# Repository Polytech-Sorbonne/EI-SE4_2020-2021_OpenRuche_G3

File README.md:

# Projet Open Ruche 2020-2021

Ce projet avait pour but de concevoir une ruche connectée afin de vérifier la production de miel des abeilles ainsi que leur bonne santé. Il a été conduit de     
septembre 2020 jusque janvier 2021 par quatre élèves de Polytech Sorbonne EISE4 : Clément Leboulenger, Edouard Matheu, Julie Rago et Clément Roger.

Notre ruche connectée comportait un PCB utilisant un microcontrôleur L432KC et implémentait différents capteurs et fonctionnalités:

  - Un capteur mesurant la température et l'humidité extérieures (le DHT22)
  - Un capteur mesurant la température intérieure (le DS18B20)
  - Une station météo mesurant la vitesse du vent (la LEXCA007)
  - Un capteur de poids (le HX711)
  - Un boitier étanche et facile d'utilisation comportant un bouton ON / OFF et une LED
  - Une mesure du pourcentage de la batterie
  - Une transmission des données sur une plateforme de visualisation des données (Ubidots)
  - Une application d'alertes envoyant des mails au client en cas de problème
 
Tous les codes sources ont été écrits sur mbed et sont disponibles dans le dossier [src](src) 

## Etape 1 : Prototype sur LABDEC

Afin de reproduire le prototype sur labdec il suffit de reproduire le branchement suivant puis de charger le code sur le microcontrôleur avec MBED.

## Etape 2 : Visualisation des données

Afin de vérifier le bon fonctionnement du prototype il faut pouvoir visualiser les données reçues. Une première solution est d'afficher ces dernières en série sur le terminal, néanmoins ceci n'est pas viable à long terme.

Nous avons utilisé la plateforme Ubidots qui permet une grande diversité de widgets. Pour cela il faut d'abord programmer le callback. Pour cela, nous vous invitons à suivre ce [tutoriel](https://www.google.com/url?sa=t&rct=j&q=&esrc=s&source=web&cd=&cad=rja&uact=8&ved=2ahUKEwjIvd3LoabuAhWS3eAKHfLjBFkQFjAAegQIAxAC&url=http%3A%2F%2Fhelp.ubidots.com%2Fen%2Farticles%2F924209-setup-your-sigfox-callback-to-talk-with-ubidots-cloud&usg=AOvVaw0ofYeG-8WFQl4HqIhr2u7Q).

Ensuite il suffira de programmer le callback comme suivant :

## Etape 3 : Création du PCB

Afin d'obtenir un produit final robuste et résistant il convient de concevoir un PCB (ou circuit imprimé).

Le nôtre a été réalisé sur Kicad, tous les fichiers de conception étant présents [ici](kicad_pcb)

## Etape 4 : Branchements sur PCB

Il vous faut maintenant souder les composants (connecteurs Grove, headers ...) et brancher les différents capteurs sur le PCB comme suit :

**Après** avoir chargé le code sur le microcontrôleur (car une fois fait vous ne pourrez plus charger de code dessus) il vous faudra néanmoins déssouder des solder bridges sur le microcontrôleur afin de réduire la consommation du système et permettre l'accès du microcontrôleur à certaines pins. 

Les solder bridges à retirer sont les suivants :

  - SB9
  - SB14
  - SB16
  - SB18
  
Les solder bridges sont inscrits directement sur le microcontrôleur ou vous pouvez trouver l'emplacement de ces derniers sur l'image suivante

Après avoir suivi ces étapes, il ne vous reste plus qu'à mettre le tout dans une boîte étanche.

Vous pouvez également allonger les câbles avec des gaines, isoler le tout avec de la colle à chaud et faire des plateformes pour certains capteurs pour qu'ils tiennent mieux sur la ruche.

Pour tout détail sur l'utilisation, veuillez vous référer à la [notice d'utilisation](documentation_technique/Notice.pdf)

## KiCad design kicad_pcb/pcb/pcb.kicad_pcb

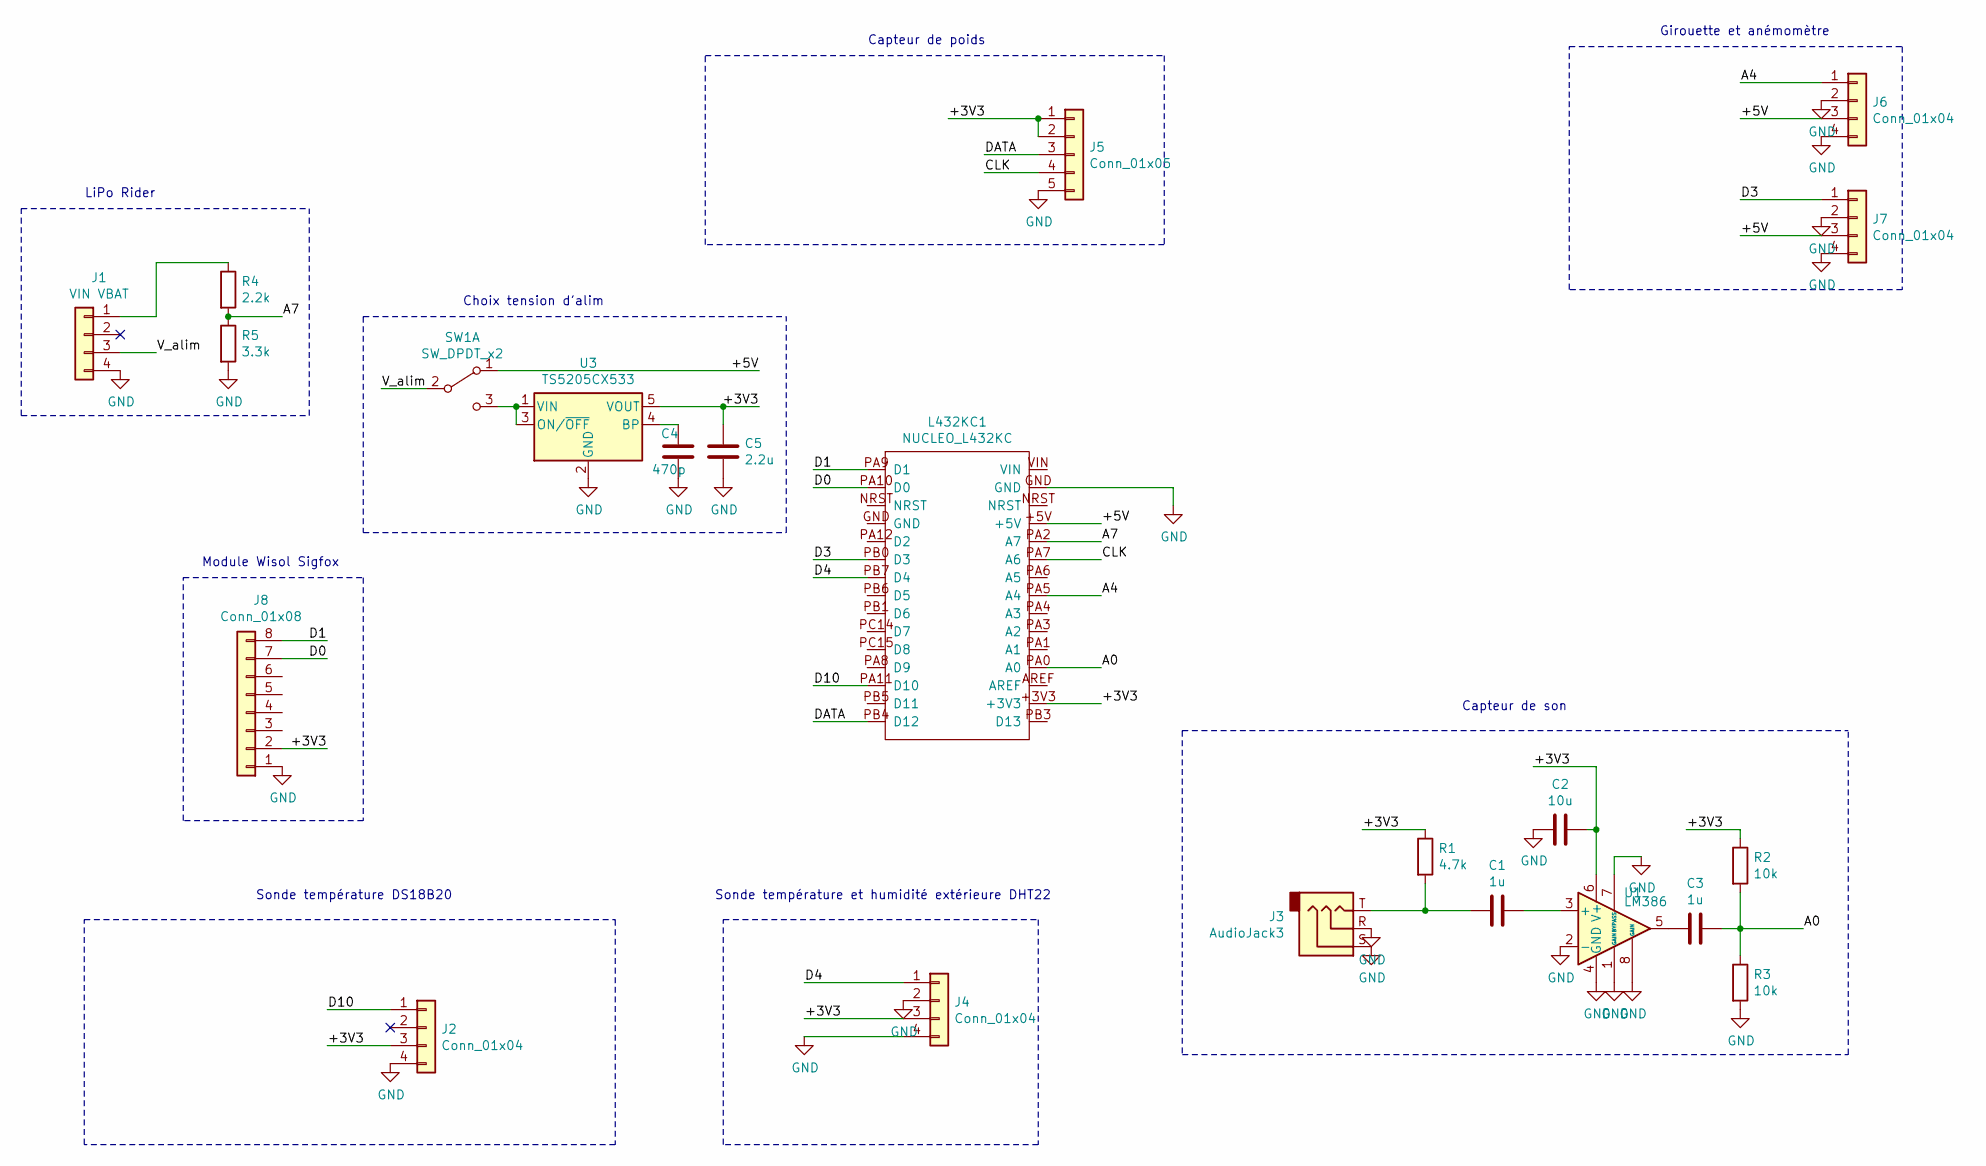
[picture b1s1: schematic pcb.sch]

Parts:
C1, C3: 1u; CP_Radial_D6.3mm_P2.50mm
C2: 10u; CP_Radial_D5.0mm_P2.00mm
C4: 470p; C_0805_2012Metric_Pad1.18x1.45mm_HandSolder
C5: 2.2u; C_0805_2012Metric_Pad1.18x1.45mm_HandSolder
J1: VIN VBAT; PinHeader_1x04_P2.00mm_Vertical
J2, J4, J6, J7: Conn_01x04; PinHeader_1x04_P2.00mm_Vertical
J3: AudioJack3; Jack_3.5mm_Ledino_KB3SPRS_Horizontal
J5: Conn_01x05; PinHeader_1x05_P2.54mm_Vertical
J8: Conn_01x08; PinHeader_1x08_P2.54mm_Vertical
L432KC1: NUCLEO_L432KC; MODULE_NUCLEO-L432KC
R1: 4.7k; R_Axial_DIN0207_L6.3mm_D2.5mm_P10.16mm_Horizontal
R2, R3: 10k; R_Axial_DIN0207_L6.3mm_D2.5mm_P10.16mm_Horizontal
R4: 2.2k; R_Axial_DIN0207_L6.3mm_D2.5mm_P10.16mm_Horizontal
R5: 3.3k; R_Axial_DIN0207_L6.3mm_D2.5mm_P10.16mm_Horizontal
SW1: SW_DPDT_x2; PinHeader_2x02_P2.54mm_Vertical
U1: LM386; DIP794W45P254L959H508Q8
U3: TS5205CX533; SOT-23-5

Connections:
/+3V3: C2.1, C5.1, J2.3, J4.3, J5.1, J5.2, J8.2, L432KC1.+3V3, R1.1, R2.1, U1.6 (V+), U3.5 (VOUT)
/+5V: J6.3, J7.3, L432KC1.+5V, SW1.1 (A)
/A0: C3.1, L432KC1.PA0 (A0), R2.2, R3.1
/A4: J6.1, L432KC1.PA5 (A4)
/A7: L432KC1.PA2 (A7), R4.2, R5.1
/CLK: J5.4, L432KC1.PA7 (A6)
/D0: J8.7, L432KC1.PA10 (D0)
/D1: J8.8, L432KC1.PA9 (D1)
/D3: J7.1, L432KC1.PB0 (D3)
/D4: J4.1, L432KC1.PB7 (D4)
/D10: J2.1, L432KC1.PA11 (D10)
/DATA: J5.3, L432KC1.PB4 (D12)
/V_alim: J1.3, SW1.2 (B)
GND: C2.2, C4.2, C5.2, J1.4, J2.4, J3.R, J3.S, J4.2, J4.4, J5.5, J6.2, J6.4, J7.2, J7.4, J8.1, L432KC1.GND, R3.2, R5.2, U1.1 (GAIN), U1.2 (-), U1.4 (GND), U1.7 (BYPASS), U1.8 (GAIN), U3.2 (GND)
unnamed: C1.1, U1.3 (+)
unnamed: C1.2, J3.T, R1.2
unnamed: C3.2, U1.5
unnamed: C4.1, U3.4 (BP)
unnamed: J1.1, R4.1
unnamed: SW1.3 (C), U3.1 (VIN), U3.3 (ON/~OFF~)

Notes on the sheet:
Sonde température DS18B20
Sonde température et humidité extérieure DHT22
Capteur de son
Girouette et anémomètre
LiPo Rider
Capteur de poids
Module Wisol Sigfox
Choix tension d'alim

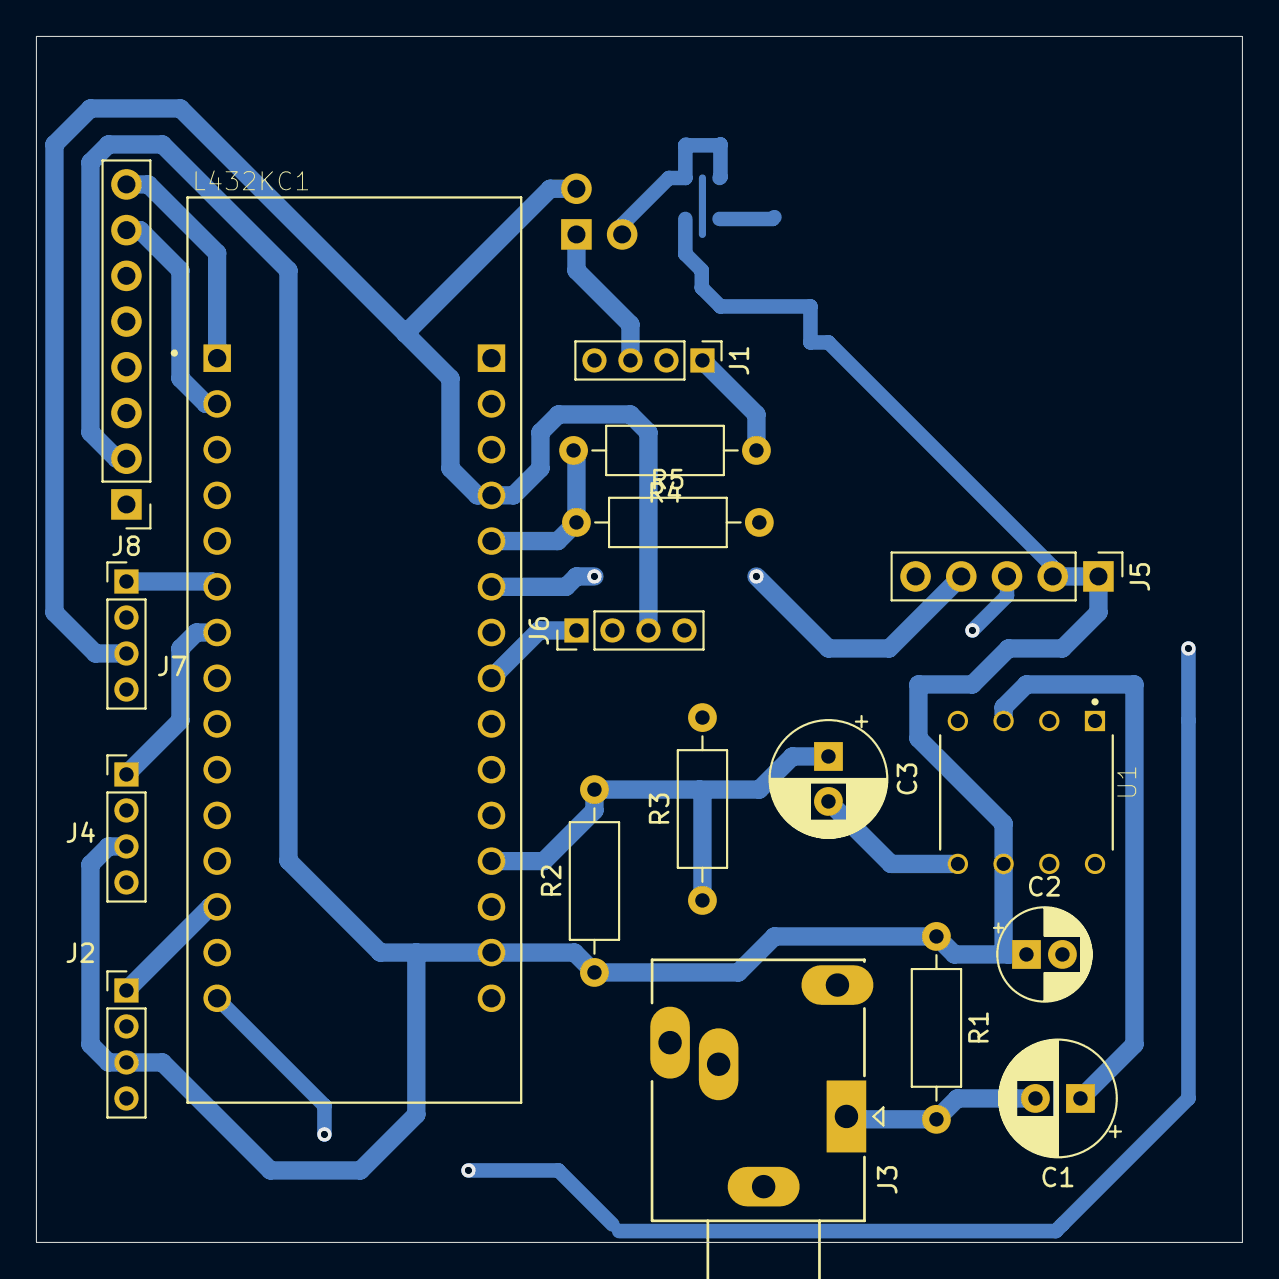
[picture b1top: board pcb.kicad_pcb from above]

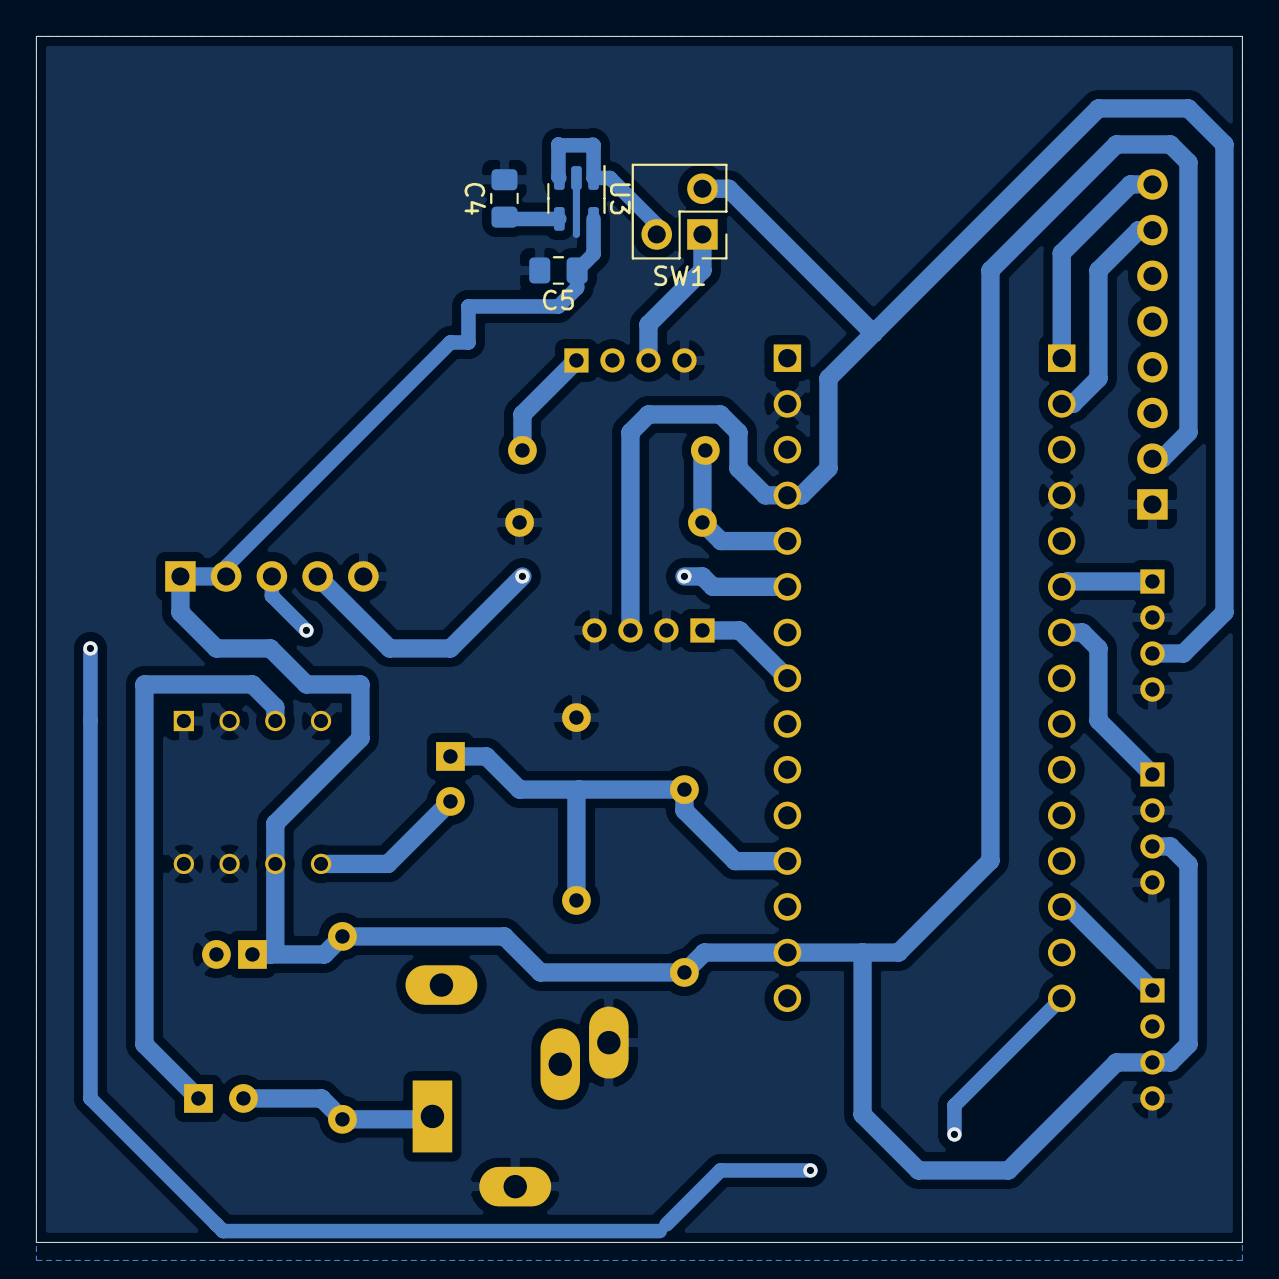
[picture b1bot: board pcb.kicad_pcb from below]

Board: 2 copper layers, 67.0 x 67.0 mm, 22 parts (4 on the bottom side), 20 nets.

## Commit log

2021-01-25 Commit initial
